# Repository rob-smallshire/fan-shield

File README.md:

fan-shield
==========

A fan controller shield based on the MAX6651 controller

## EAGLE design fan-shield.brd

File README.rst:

fan-shield
==========

A fan controller shield based on the MAX6651 controller.

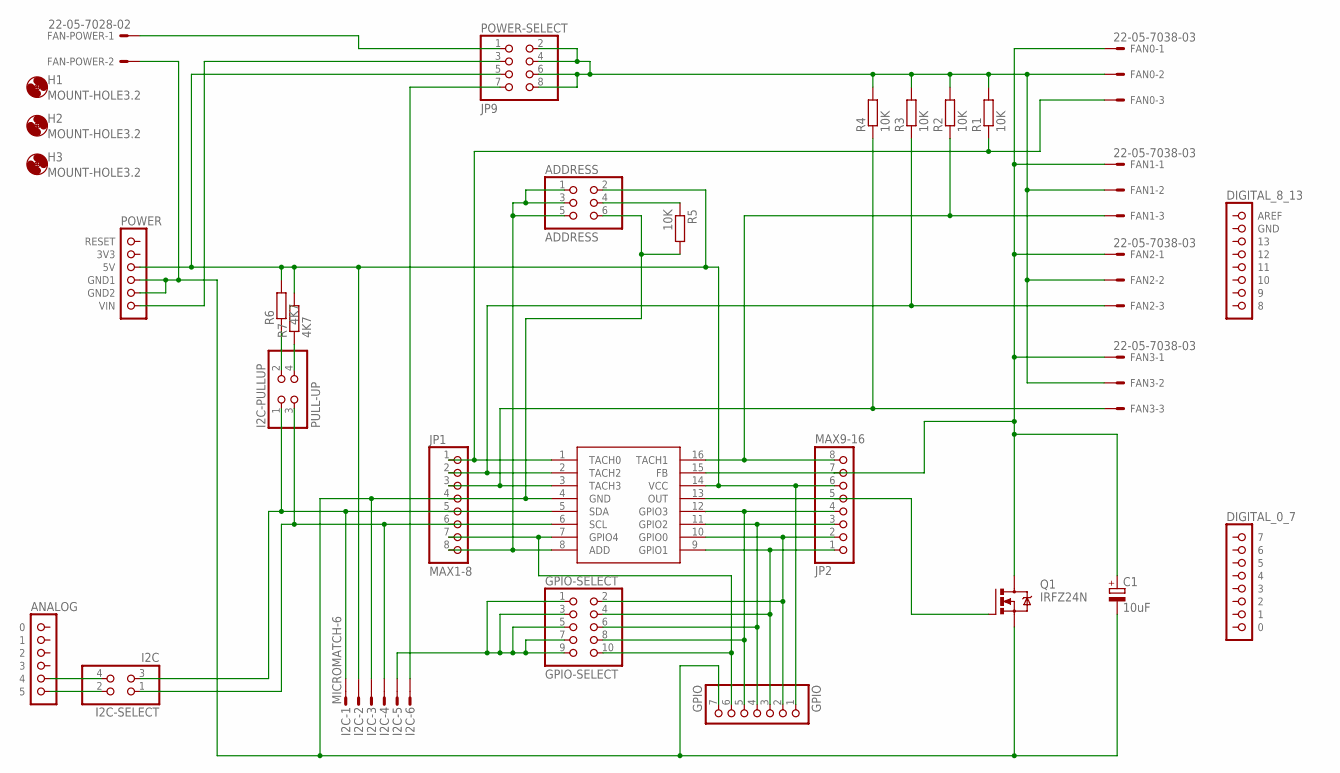
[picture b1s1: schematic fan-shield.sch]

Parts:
ADDRESS: ADDRESS; 2X03
C1: 10uF; E2,5-6
FAN0, FAN1, FAN2, FAN3: 22-05-7038-03; 7395-03
FAN-POWER: 22-05-7028-02; 7395-02
GPIO: GPIO; 1X07/90
GPIO-SELECT: GPIO-SELECT; 2X05
H1, H2, H3: MOUNT-HOLE3.2; 3,2
I2C: MICROMATCH-6
I2C-PULLUP: PULL-UP; 2X02
I2C-SELECT: I2C; 2X02/90
JP1: MAX1-8; 1X08
JP2: MAX9-16; 1X08
MAX6651: MAX6651; QSOP16
POWER-SELECT: JP9; 2X04
Q1: IRFZ24N; TO200AB
R1, R2, R3, R4, R5: 10K; 0207/10
R6, R7: 4K7; 0207/10
U$1: POWER; 1X06
U$2: ANALOG; 1X06
U$3: DIGITAL_0_7; 1X08
U$4: DIGITAL_8_13; 1X08

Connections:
5V: ADDRESS.2, GPIO.1, I2C.2, JP2.6, MAX6651.14 (VCC), POWER-SELECT.5, R6.2, R7.2, U$1.3 (5V)
ADD: ADDRESS.1, ADDRESS.3, ADDRESS.5, JP1.8, MAX6651.8 (ADD)
FEEDBACK: C1.+, FAN0.1, FAN1.1, FAN2.1, FAN3.1, JP2.7, MAX6651.15 (FB), Q1.D
GND: ADDRESS.6, C1.-, FAN-POWER.2, GPIO.7, I2C.3, JP1.4, MAX6651.4 (GND), Q1.S, R5.2, U$1.4 (GND1), U$1.5 (GND2)
GPIO0: GPIO.2, GPIO-SELECT.2, JP2.2, MAX6651.10 (GPIO0)
GPIO1: GPIO.3, GPIO-SELECT.4, JP2.1, MAX6651.9 (GPIO1)
GPIO2: GPIO.4, GPIO-SELECT.6, JP2.3, MAX6651.11 (GPIO2)
GPIO3: GPIO.5, GPIO-SELECT.8, JP2.4, MAX6651.12 (GPIO3)
GPIO4: GPIO.6, GPIO-SELECT.10, JP1.7, MAX6651.7 (GPIO4)
GPIO-CONNECT: GPIO-SELECT.1, GPIO-SELECT.3, GPIO-SELECT.5, GPIO-SELECT.7, GPIO-SELECT.9, I2C.5
I2C: I2C-SELECT.4, U$2.5 (4)
unnamed: I2C-PULLUP.2, R6.1
unnamed: I2C-PULLUP.4, R7.1
unnamed: ADDRESS.4, R5.1
unnamed: FAN-POWER.1, POWER-SELECT.1
OUT: JP2.5, MAX6651.13 (OUT), Q1.G
SCL: I2C.4, I2C-PULLUP.3, I2C-SELECT.1, JP1.6, MAX6651.6 (SCL)
SCL-ARDUINO: I2C-SELECT.2, U$2.6 (5)
SDA: I2C.1, I2C-PULLUP.1, I2C-SELECT.3, JP1.5, MAX6651.5 (SDA)
TACH0: FAN0.3, JP1.1, MAX6651.1 (TACH0), R1.1
TACH1: FAN1.3, JP2.8, MAX6651.16 (TACH1), R2.1
TACH2: FAN2.3, JP1.2, MAX6651.2 (TACH2), R3.1
TACH3: FAN3.3, JP1.3, MAX6651.3 (TACH3), R4.1
VAUX: I2C.6, POWER-SELECT.7
VFAN: FAN0.2, FAN1.2, FAN2.2, FAN3.2, POWER-SELECT.2, POWER-SELECT.4, POWER-SELECT.6, POWER-SELECT.8, R1.2, R2.2, R3.2, R4.2
VIN: POWER-SELECT.3, U$1.6 (VIN)

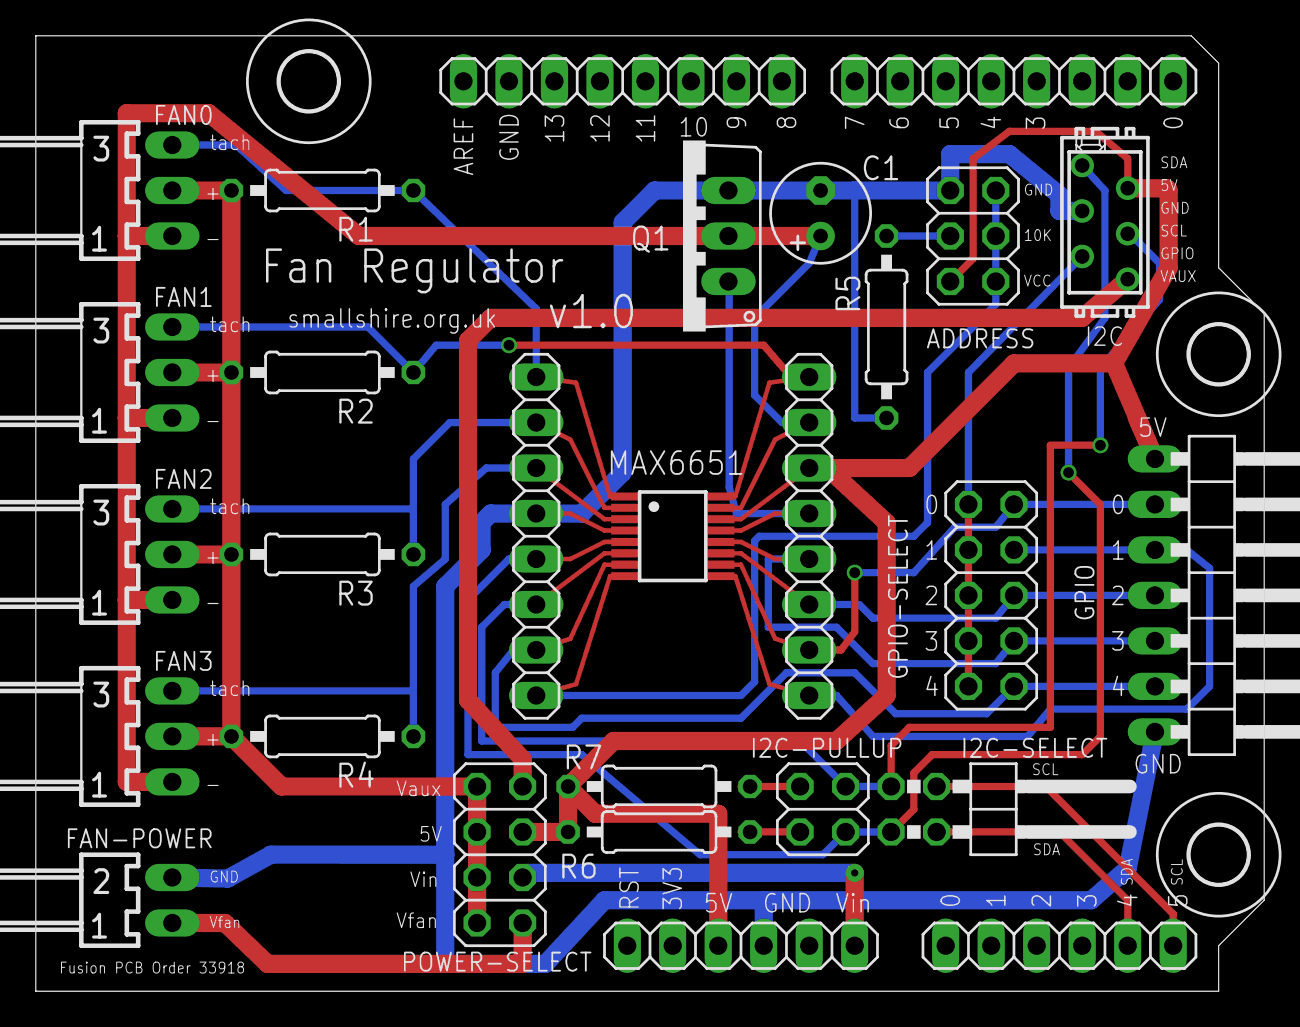
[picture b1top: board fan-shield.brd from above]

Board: 2 copper layers, 68.6 x 53.3 mm, 31 parts (0 on the bottom side), 26 nets.

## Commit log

2013-05-17 Original files from canisp
2013-05-17 Upgraded to Eagle 6
